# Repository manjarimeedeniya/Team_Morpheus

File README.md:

# Weighing Scale Using Load Cells

**EN2091 Analog Project** — Department of Electronic and Telecommunication Engineering, University of Moratuwa, Sri Lanka

---

## 👥 Team Morpheus 

| Name | GitHub Link |
|---|---|
| Gunarathne K.T.M.B | https://github.com/ThidaswinGunarathna |
| Jayaweera N.S | https://github.com/NisalJayaweera |
| Meedeniya M.M.H | https://github.com/manjarimeedeniya |
| Ranawaka R.A.C.D | https://github.com/chaniruranawaka |

---

## 📋 Project Overview

An electronic weighing scale designed and implemented using a **strain gauge load cell**. The system captures the low-level differential voltage produced by the load cell, amplifies and filters it through an analog signal conditioning circuit, and displays the corresponding weight on a **16×2 LCD screen** via an ESP32 microcontroller.

**Key Specifications:**
- Maximum measuring capacity: **10 kg**
- Power input: **230V AC mains**
- Full-scale output voltage: **3V** (at 10 kg)
- Display: **16×2 LCD** (via I²C interface)
- Microcontroller: **ESP-WROOM-32E (ESP32)**

---

## 📸 Final Product

---

## 🏗️ System Architecture

```
230V AC Supply
      │
      ▼
Step-Down Transformer (230V → 13.5V AC)
      │
      ▼
Power Supply Circuit (Delon Doubler + Regulators)
      │
      ├──► +12V, -12V (for op-amps & load cell excitation)
      ├──► +5V  (for LCD)
      └──► +3.3V (for ESP32)

Load Cell (Wheatstone Bridge)
      │
      ▼
INA114 Instrumentation Amplifier (Gain ≈ 100)
      │
      ▼
Zero Adjust Circuit (TL084 op-amp + potentiometer)
      │
      ▼
Span Adjust Circuit (TL084 op-amp, variable gain)
      │
      ▼
3rd Order Sallen-Key Low-Pass Filter (10 Hz cutoff, TL072)
      │
      ▼
ESP32 ADC → Weight Calculation → 16×2 LCD Display
```

---

## ⚙️ Circuit Design

### Load Cell
- Type: Strain-gauge based, Wheatstone bridge configuration
- Capacity: 20 kg (used up to 10 kg)
- Rated output: 2.0 ± 0.15 mV/V
- Excitation voltage: 12V DC

### Amplifier Circuit
| Stage | Component | Purpose |
|---|---|---|
| Instrumentation Amplifier | INA114 | Amplifies differential load cell output (gain ≈ 100), high CMRR (~115 dB) |
| Zero Adjust | TL084 + 100kΩ potentiometer | Cancels offset voltage at zero load |
| Span Adjust | TL084 + 100kΩ potentiometer | Calibrates full-scale output to 3V at 10 kg |
| Low-Pass Filter | TL072 (3rd order Sallen-Key) | Cuts off noise above 10 Hz |

### Power Supply Circuit
| Regulator | Output | Powers |
|---|---|---|
| LM7812 | +12V | Load cell, INA114, op-amps |
| LM7912 | -12V | Op-amps (dual supply) |
| LM7805 | +5V | LCD display |
| AMS1117 | +3.3V | ESP32 chip |

The Delon Doubler circuit is used to generate the dual-supply (±) voltage from the single-rail transformer output.

---

## 🧰 Components List

### Amplifier Circuit
| Component | Quantity |
|---|---|
| INA114 Instrumentation Amplifier IC | 1 |
| TL084 Quad Op-Amp IC | 1 |
| TL072 Dual Op-Amp IC | 1 |
| 470Ω Resistor | 1 |
| 10kΩ Resistors | 8 |
| 100kΩ Resistor | 1 |
| 110kΩ Resistor | 1 |
| 11kΩ Resistor | 1 |
| 33kΩ Resistor | 1 |
| 100kΩ Variable Resistors (Potentiometers) | 2 |
| 0.1µF Capacitors | 5 |
| 0.68µF Capacitor | 1 |
| 1.5µF Capacitor | 1 |
| Push Buttons | 2 |
| JST Wire Connectors 2.54mm (4-pin) | 3 |
| JST Wire Connectors 2.54mm (5-pin) | 1 |

### Power Supply Circuit
| Component | Quantity |
|---|---|
| 230V AC to 13.5V AC Step-Down Transformer | 1 |
| 1N4007 Diodes | 2 |
| 50V 1000µF Capacitors | 2 |
| 50V 470µF Capacitors | 2 |
| 50V 100µF Capacitors | 2 |
| 50V 10µF Capacitors | 2 |
| LM7812 +12V Regulator | 1 |
| LM7912 -12V Regulator | 1 |
| LM7805 +5V Regulator | 1 |
| AMS1117 3.3V Regulator | 1 |
| Switch | 1 |
| LED | 1 |
| JST Wire Connectors 2.54mm (2-pin) | 3 |
| JST Wire Connectors 2.54mm (5-pin) | 1 |

### Other Components
| Component | Quantity |
|---|---|
| 20kg Strain-Gauge Load Cell | 1 |
| ESP-WROOM-32E Microcontroller | 1 |
| 16×2 LCD Display | 1 |
| IIC/I²C Serial Interface Module for LCD | 1 |
| 3-pin AC Power Base | 1 |
| Power Cable | 1 |

---

---

## 🔧 Calibration Procedure

1. **Zero Adjustment** — With no load on the scale, adjust the zero-adjust potentiometer until the LCD reads `0.00 kg`.
2. **Span Adjustment** — Place a known 10 kg reference weight on the platform. Adjust the span-adjust potentiometer until the display reads `10.00 kg`.
3. The system is now calibrated across the full measurement range.

---

## 💻 Firmware

The ESP32 firmware reads the analog voltage output from the signal conditioning circuit via its built-in ADC, applies the calibration mapping, and sends the weight value to the 16×2 LCD over I²C.

**Upload Instructions:**
1. Install the [Arduino IDE](https://www.arduino.cc/en/software) and add ESP32 board support.
2. Install the `LiquidCrystal_I2C` library via the Library Manager.
3. Open `firmware/main.ino`, select your board (`ESP32 Dev Module`) and COM port.
4. Upload the sketch.

---

## 🚧 Challenges Encountered

- **Capacitor availability** — 0.68µF and 1.5µF electrolytic capacitors were unavailable locally. Ceramic equivalents were used, but their lead spacing required manual wire extensions to fit the PCB footprint.
- **Electromagnetic interference** — After full assembly, the amplifier output showed an unexpected ~60V peak-to-peak sine wave. This was traced to electromagnetic radiation from the mains transformer coupling into nearby signal wires. The fix involved additional transformer shielding with a metal plate and shortening signal wire runs.
- **Platform deformation** — The initial wooden weighing platform deformed under load and made contact with the base, introducing measurement errors. It was replaced with a rigid acrylic plate with a larger clearance gap.

---

## 🔭 Future Improvements

- **Battery operation** — Replace mains power with a low-power design for portability.
- **Wireless connectivity** — Add Bluetooth or Wi-Fi (ESP32 already supports this) for remote monitoring and data logging to a mobile app or PC.

---

## 👨‍💼 Contributions

| Member | Contributions |
|---|---|
| Gunarathne K.T.M.B  | ESP32 firmware, LCD integration, soldering, assembly, component selection |
| Jayaweera N.S  | PCB design, soldering, assembly, component selection |
| Meedeniya M.M.H  | Circuit design, enclosure design, assembly, component selection |
| Ranawaka R.A.C.D  | Enclosure span design, soldering, assembly, component selection |

---

## 🙏 Acknowledgements

We sincerely thank **Dr. Sampath Perera** and supervisor **Mr. Viruthshaan** for their guidance throughout the project. We also appreciate the feedback from **Dr. Jayathu Samarawickrama**, **Dr. Pranjeevan Kulasingham**, **Dr. Wageesha N. Manamperi**, and **Mr. Lathika Wathsara** during the project evaluation. Thanks to the academic and non-academic staff of the ENTC Department, University of Moratuwa, for their support and facilities.

---

## 📚 References

1. INA114 Datasheet — https://www.alldatasheet.com/datasheet-pdf/view/847617/TI1/INA114.html
2. TL084 Datasheet — https://www.alldatasheet.com/datasheet-pdf/view/25385/STMICROELECTRONICS/TL084.html
3. TL072 Datasheet — https://www.alldatasheet.com/datasheet-pdf/view/28775/TI/TL072.html
4. LM7812 Datasheet — https://www.alldatasheet.com/datasheet-pdf/pdf/838008/TI1/LM7812.html

---

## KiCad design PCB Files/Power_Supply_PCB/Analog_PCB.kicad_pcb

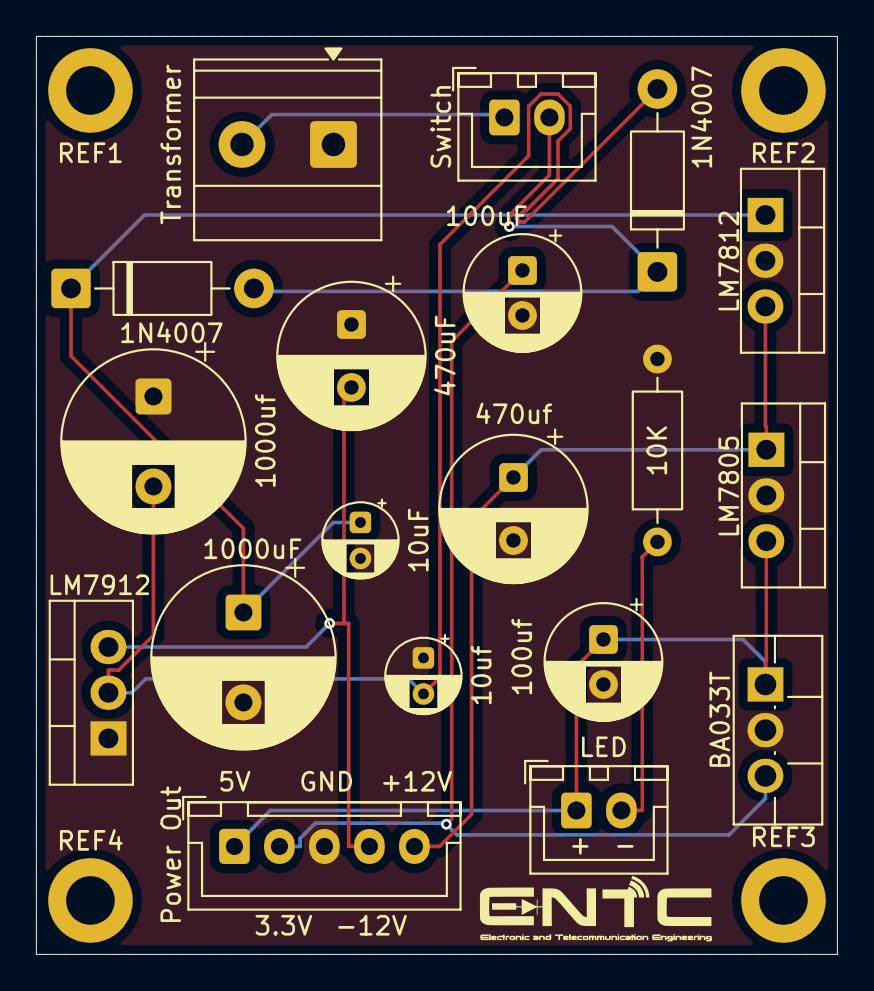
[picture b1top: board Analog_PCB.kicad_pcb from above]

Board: 2 copper layers, 44.5 x 51.0 mm, 24 parts (0 on the bottom side), 10 nets.

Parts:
1N4007: 1N4007; D_DO-41_SOD81_P10.16mm_Horizontal
10K: R; R_Axial_DIN0207_L6.3mm_D2.5mm_P10.16mm_Horizontal
10uF, 10uf: C; CP_Radial_D4.0mm_P2.00mm
100uF, 100uf: C; CP_Radial_D6.3mm_P2.50mm
470uF, 470uf: C; CP_Radial_D8.0mm_P3.50mm
1000uF, 1000uf: C; CP_Radial_D10.0mm_P5.00mm
BA033T: BA033T; TO-220F-3_Vertical
D2: 1N4007; D_DO-41_SOD81_P10.16mm_Horizontal
LED: Conn_01x02; JST_XH_B2B-XH-A_1x02_P2.50mm_Vertical
LM7805: LM7805_TO220; TO-220-3_Vertical
LM7812: LM7812_TO220; TO-220-3_Vertical
LM7912: LM7912_TO220; TO-220-3_Vertical
Power Out: Conn_01x05; JST_XH_B5B-XH-A_1x05_P2.50mm_Vertical
REF1, REF2, REF3, REF4: MountingHole_2.7mm_M2.5_DIN965_Pad
Switch: Conn_01x02; JST_XH_B2B-XH-A_1x02_P2.50mm_Vertical
Team Morpheus: LOGO; ENTC_Logo
Transformer: Screw_Terminal_01x02; TerminalBlock_Phoenix_MKDS-1,5-2-5.08_1x02_P5.08mm_Horizont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

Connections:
GND: 10K.2, 10uF.2, 10uf.1, 100uF.2, 100uf.2, 470uF.1, 470uf.2, 1000uF.2, 1000uf.1, BA033T.2 (GND), LM7805.2 (GND), LM7812.2 (GND), LM7912.1 (GND), Power Out.3, Transformer.1
unnamed: 1N4007.2 (A), 10uf.2, 1000uf.2, LM7912.2 (VI)
unnamed: 1N4007.1 (K), D2.2 (A), Switch.2
unnamed: 10uF.1, 1000uF.1, D2.1 (K), LM7812.1 (VI)
unnamed: Switch.1, Transformer.2
unnamed: 100uf.1, BA033T.1 (VI), LED.1, LM7805.3 (VO), Power Out.1
unnamed: 100uF.1, BA033T.3 (VO), Power Out.2
unnamed: 470uF.2, LM7912.3 (VO), Power Out.4
unnamed: 470uf.1, LM7805.1 (VI), LM7812.3 (VO), Power Out.5
unnamed: 10K.1, LED.2

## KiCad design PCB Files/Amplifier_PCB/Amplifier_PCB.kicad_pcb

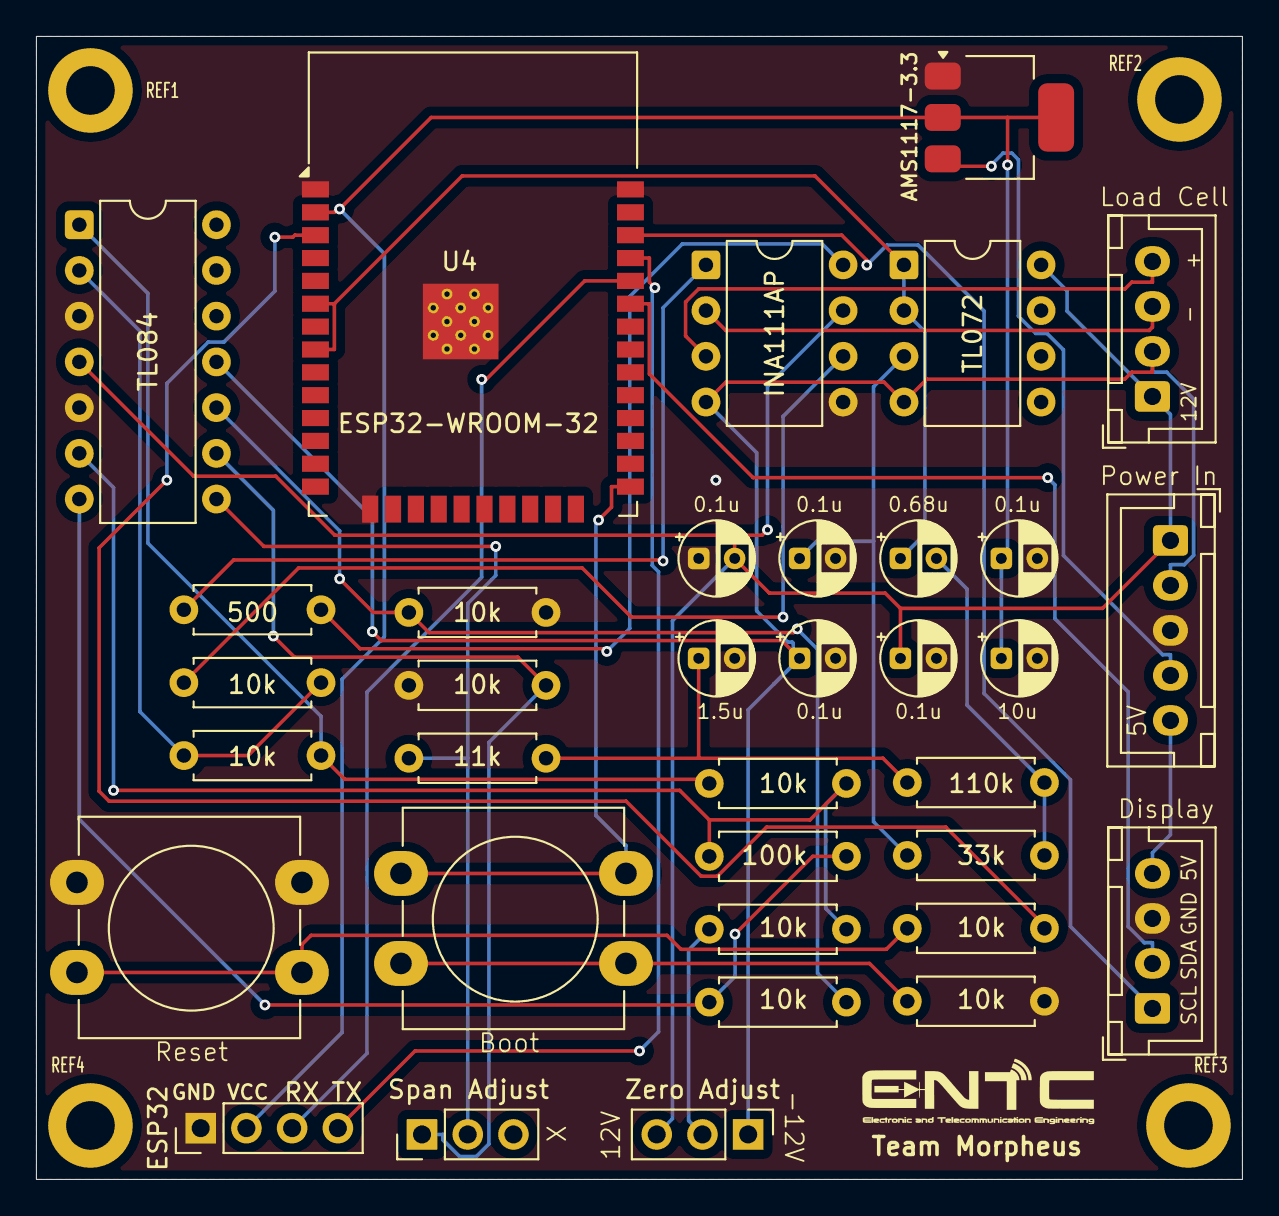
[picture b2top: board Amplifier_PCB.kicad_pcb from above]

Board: 2 copper layers, 67.0 x 63.5 mm, 40 parts (0 on the bottom side), 31 nets.

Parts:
10k, 10k#2, 10k#3, 10k#4, 10k#5, 33k, 110k: 10k; R_Axial_DIN0207_L6.3mm_D2.5mm_P7.62mm_Horizontal
100k: 100k; R_Axial_DIN0207_L6.3mm_D2.5mm_P7.62mm_Horizontal
C1, C3, C4, C6, C7: 0.1u; CP_Radial_D4.0mm_P2.00mm
C2: 1.5u; CP_Radial_D4.0mm_P2.00mm
C5: 0.68u; CP_Radial_D4.0mm_P2.00mm
C8: 10u; CP_Radial_D4.0mm_P2.00mm
ESP32: GND; PinHeader_1x04_P2.54mm_Vertical
J1: Conn_01x05; JST_XH_B5B-XH-A_1x05_P2.50mm_Vertical
J2, J3: Conn_01x04; JST_XH_B4B-XH-A_1x04_P2.50mm_Vertical
R1: 500; R_Axial_DIN0207_L6.3mm_D2.5mm_P7.62mm_Horizontal
R2, R3, R8, R9: 10k; R_Axial_DIN0207_L6.3mm_D2.5mm_P7.62mm_Horizontal
R11: 11k; R_Axial_DIN0207_L6.3mm_D2.5mm_P7.62mm_Horizontal
REF1, REF2, REF3, REF4: MountingHole_2.7mm_M2.5_DIN965_Pad
SW1, SW2: SW_Push; SW_PUSH-12mm_Wuerth-430476085716
Span Adjust: R_Variable; PinHeader_1x03_P2.54mm_Vertical
Team Morpheus: LOGO; ENTC_Logo
U1: INA111AP; DIP-8_W7.62mm
U2: TL084; DIP-14_W7.62mm
U3: TL072; DIP-8_W7.62mm
U4: ESP32-WROOM-32
U5: AMS1117-3.3; SOT-223-3_TabPin2
Zero Adjust: R_Potentiometer; PinHeader_1x03_P2.54mm_Vertical

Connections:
/3.3V: J1.4, U5.3 (VI)
/5V: J1.5, J3.4
/12V: C1.2, C6.1, J1.1, J2.1, U1.7 (V+), U2.4 (V+), U3.8 (V+), Zero Adjust.3
/-12V: C4.1, J1.2, J2.2, U1.4 (V-), U2.11 (V-), U3.4 (V-), Zero Adjust.1
/GND: 10k#4.2, C1.1, C2.2, C3.2, C4.2, C6.2, C7.2, C8.2, ESP32.1, J1.3, J3.3, R8.2, R9.1, SW2.1, U1.5 (REF), U2.3 (+), U2.5 (+), U4.1 (GND), U4.15 (GND), U4.38 (GND), U4.39 (GND), U5.1 (GND)
/SCL: J3.1, U4.36 (IO22)
/SDA: J3.2, U4.33 (IO21)
unnamed: 110k.1, C2.1, R11.2
unnamed: 33k.2, 110k.2, C5.2
unnamed: J2.3, U1.2 (V-IN)
unnamed: J2.4, U1.3 (V+IN)
unnamed: C7.1, C8.1, ESP32.2, U4.2 (VDD), U5.2 (VO)
unnamed: ESP32.3, U4.34 (RXD0/IO3)
unnamed: ESP32.4, U4.35 (TXD0/IO1)
unnamed: R1.1, U1.1 (RG)
unnamed: R1.2, U1.8 (RG)
unnamed: 10k#3.1, R3.2, U2.1
unnamed: 10k.1, 100k.2, U2.7
unnamed: 10k#5.1, Zero Adjust.2
unnamed: R11.1, Span Adjust.2, U2.8
unnamed: 10k#2.1, SW2.2
unnamed: 10k#4.1, SW1.2
unnamed: R2.1, U1.6 (VO)
unnamed: R2.2, R3.1, U2.2 (-)
unnamed: 10k#3.2, 10k#5.2, 100k.1, U2.6 (-)
unnamed: 10k.2, R8.1, U2.10 (+)
unnamed: R9.2, Span Adjust.1, U2.9 (-)
unnamed: 33k.1, C3.1, U3.3 (+)
unnamed: C5.1, U3.1, U3.2 (-), U4.6 (IO34), U4.8 (IO32)
unnamed: 10k#2.2, U4.3 (EN)
unnamed: SW1.1, U4.25 (IO0)

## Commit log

2026-03-25 Create one
2026-03-25 Create two
2026-03-25 Create thre
2026-03-25 Create vid
2026-03-25 Create Amplifier_PCB
2026-03-25 Create Power_Supply_PCB
2026-03-25 Create he
2026-03-25 Create hee
2026-03-25 README.md
2026-03-25 Create final_product
2026-03-25 For ReadMe
2026-03-25 Final
